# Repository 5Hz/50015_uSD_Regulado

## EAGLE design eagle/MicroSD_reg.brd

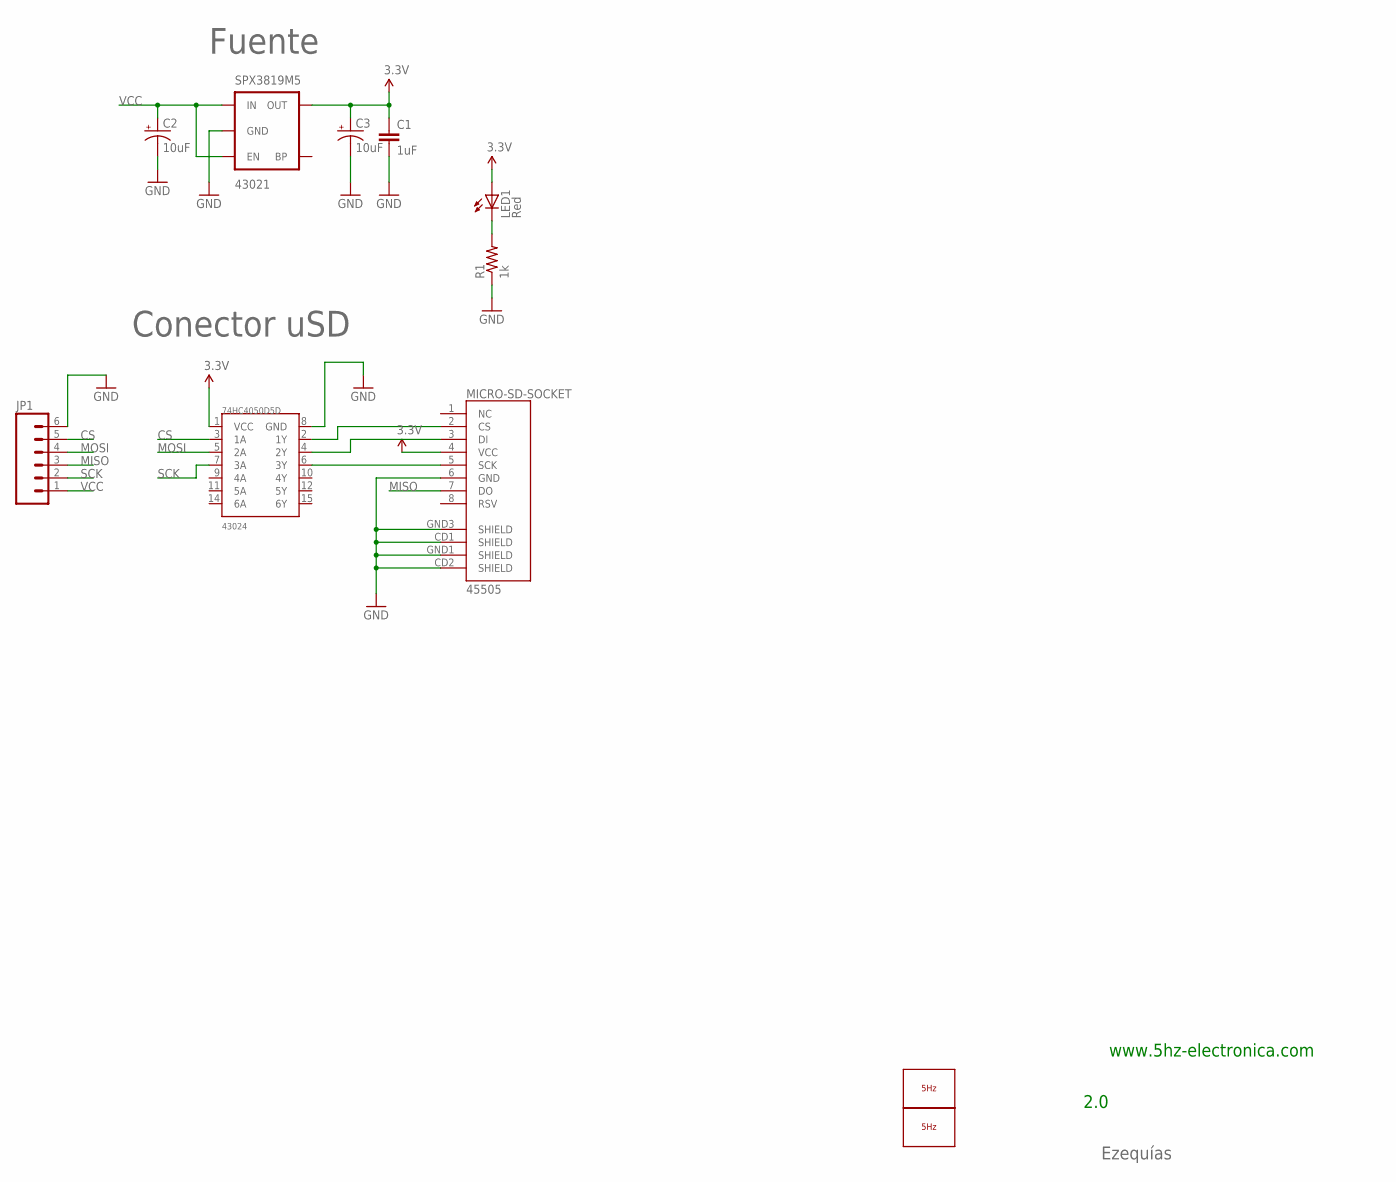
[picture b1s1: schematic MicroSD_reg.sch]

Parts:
74HC4050D5D: 43024; SO016
C1: 1uF; 0603-CAP
C2, C3: 10uF; EIA3216
JP1: M06SIP; 1X06
LED1: Red; LED-0603
LOGO1: LOGO_5HZ_MAIN_10MM; 5HZ_LOGO_MAIN_10MM
LOGO2: LOGO_5HZ_CIRC_3MM; 5HZ_LOGO_CIRC_3MM
MICRO-SD-SOCKET: 45505; MICRO-SD-SOCKET-PP
R1: 1k; 0603-RES
SPX3819M5: 43021; SOT23-5

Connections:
3.3V: 74HC4050D5D.1 (VCC), C1.1, C3.A (+), LED1.A, MICRO-SD-SOCKET.4 (VCC), SPX3819M5.5 (OUT)
CS: 74HC4050D5D.3 (1A), JP1.5
GND: 74HC4050D5D.8 (GND), C1.2, C2.C (-), C3.C (-), JP1.6, MICRO-SD-SOCKET.6 (GND), MICRO-SD-SOCKET.CD1 (SHIELD), MICRO-SD-SOCKET.CD2 (SHIELD), MICRO-SD-SOCKET.GND1 (SHIELD), MICRO-SD-SOCKET.GND3 (SHIELD), R1.1, SPX3819M5.2 (GND)
MISO: JP1.3, MICRO-SD-SOCKET.7 (DO)
MOSI: 74HC4050D5D.5 (2A), JP1.4
unnamed: 74HC4050D5D.4 (2Y), MICRO-SD-SOCKET.3 (DI)
unnamed: 74HC4050D5D.6 (3Y), MICRO-SD-SOCKET.5 (SCK)
unnamed: LED1.C, R1.2
unnamed: 74HC4050D5D.2 (1Y), MICRO-SD-SOCKET.2 (CS)
SCK: 74HC4050D5D.7 (3A), JP1.2
VCC: C2.A (+), JP1.1, SPX3819M5.1 (IN), SPX3819M5.3 (EN)

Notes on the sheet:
www.5hz-electronica.com
2.0
Fuente
Conector uSD
Ezequías

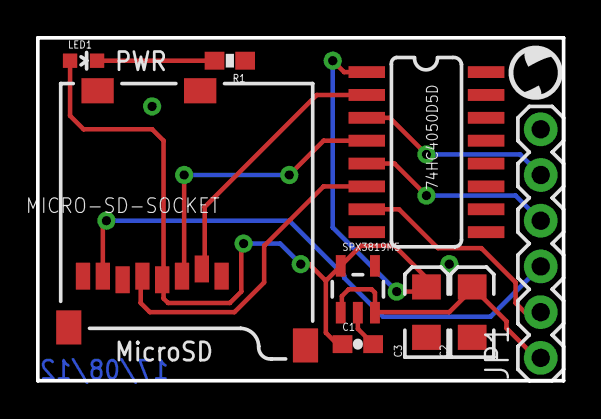
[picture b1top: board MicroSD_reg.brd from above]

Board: 2 copper layers, 29.2 x 19.1 mm, 11 parts (1 on the bottom side), 11 nets.

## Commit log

2014-01-10 creación
